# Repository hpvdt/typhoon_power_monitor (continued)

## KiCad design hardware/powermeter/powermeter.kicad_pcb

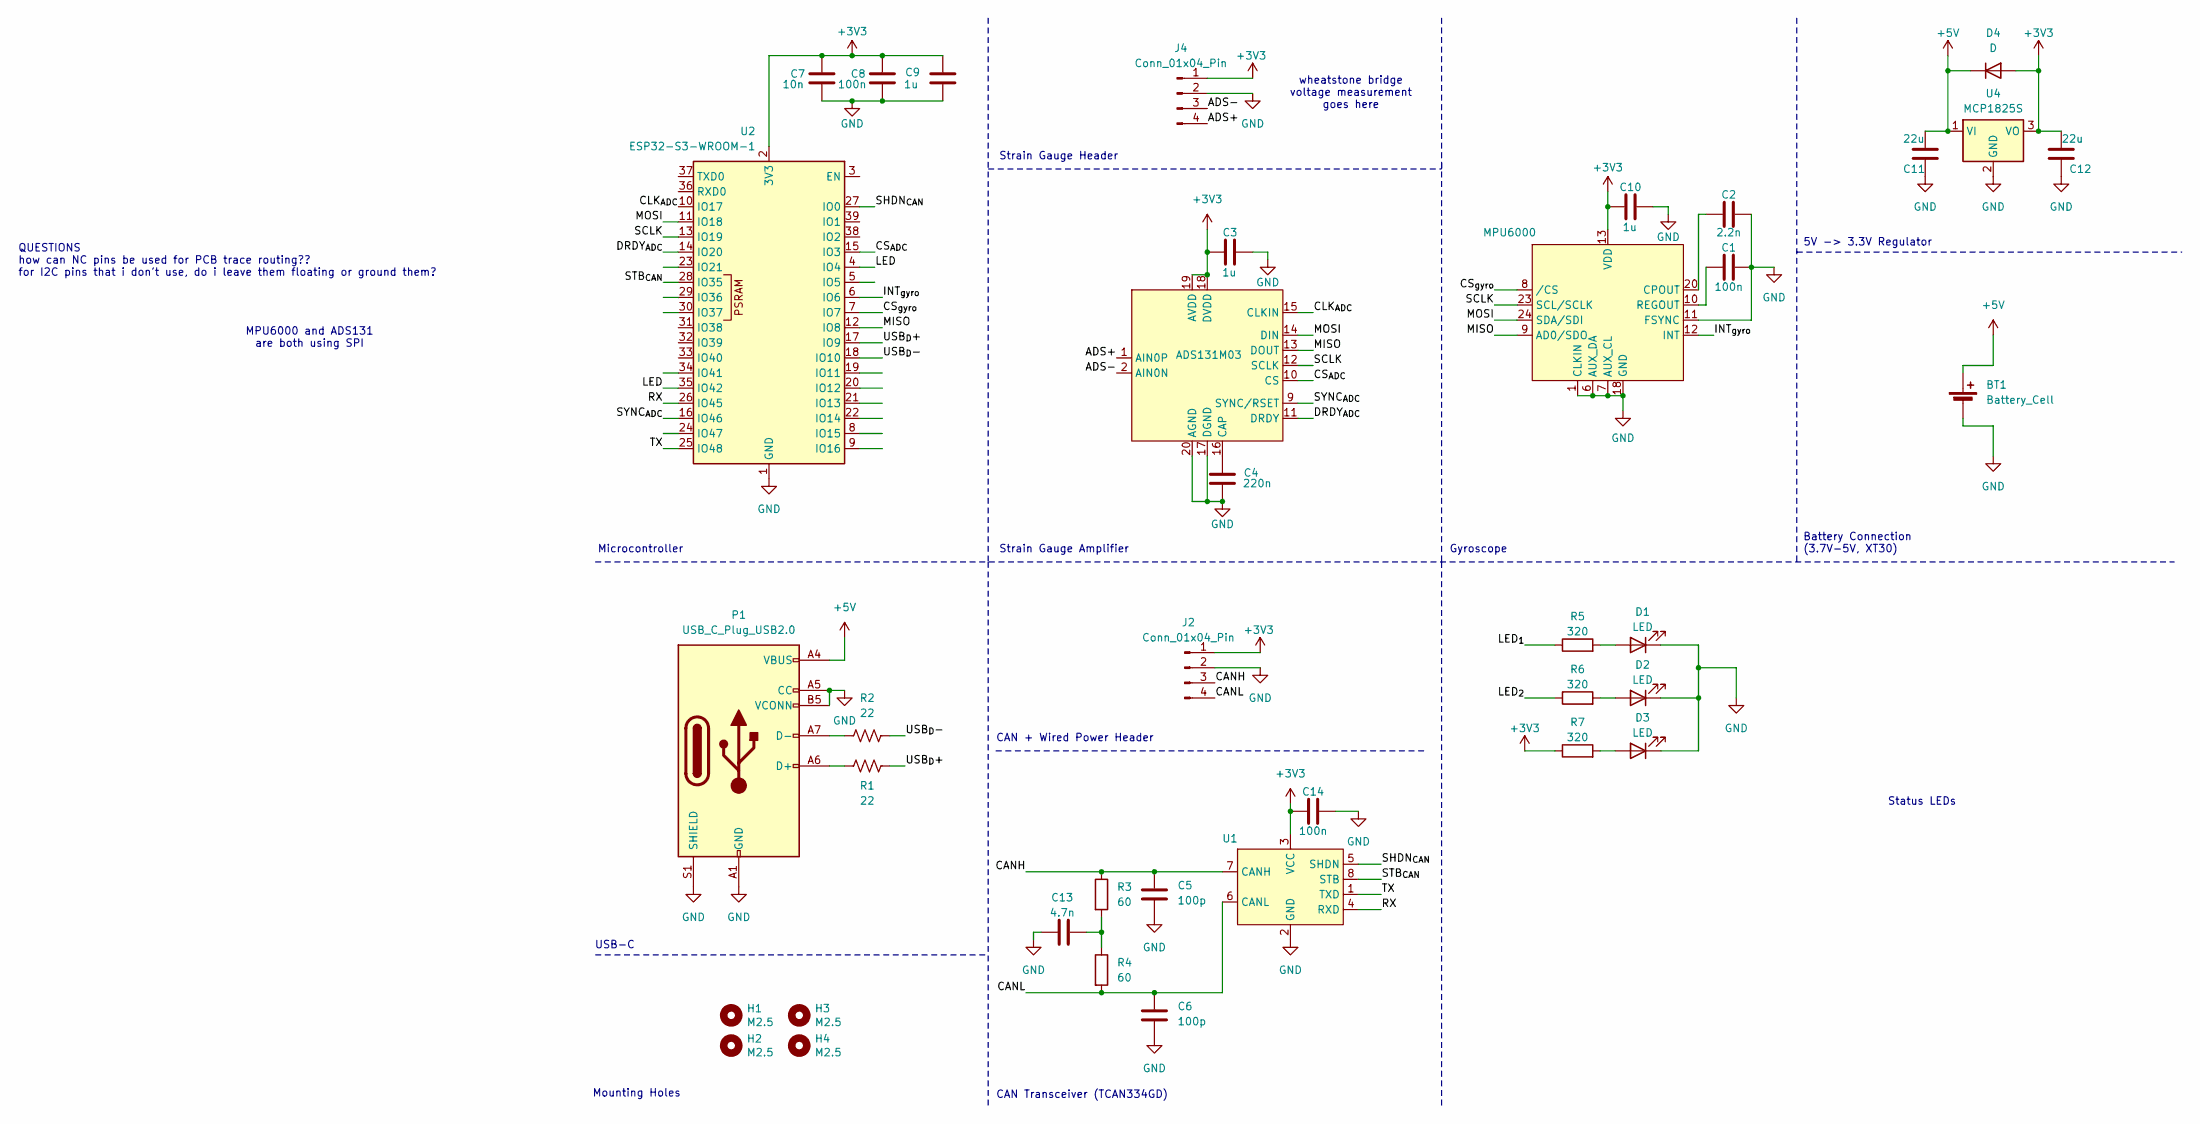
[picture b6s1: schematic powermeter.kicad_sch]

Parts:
ADS131M03: ads
BT1: Battery_Cell; AMASS_XT30U-M_1x02_P5.0mm_Vertical
C1, C8, C14: 100n; C_0402_1005Metric
C2: 2.2n; C_0402_1005Metric
C3, C9, C10: 1u; C_0402_1005Metric
C4: 220n; C_0402_1005Metric
C5, C6: 100p; C_0402_1005Metric
C7: 10n; C_0402_1005Metric
C11, C12: 22u; C_0402_1005Metric
C13: 4.7n; C_0402_1005Metric
D1, D2, D3: LED; LED_0402_1005Metric
D4: D; D_T-1_P5.08mm_Horizontal
H1, H2, H3, H4: M2.5; MountingHole_2.7mm_M2.5
J2, J4: Conn_01x04_Pin; PinSocket_1x04_P2.00mm_Vertical
MPU6000: QFN24_4X4X0P9_IVS
P1: USB_C_Plug_USB2.0; USB_C_Receptacle_HRO_TYPE-C-31-M-12
R1, R2: 22; R_0402_1005Metric
R3, R4: 60; R_0402_1005Metric
R5, R6, R7: 320; R_0402_1005Metric
U1: SO-8_3.9x4.9mm_P1.27mm
U2: ESP32-S3-WROOM-1
U4: MCP1825S; SOT-223-3_TabPin2

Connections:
+3V3: ADS131M03.18 (DVDD), ADS131M03.19 (AVDD), C3.2, C7.2, C8.2, C9.2, C10.2, C12.2, C14.2, D4.2 (A), J2.1, J4.1, MPU6000.13 (VDD), R7.1, U1.3 (VCC), U2.2 (3V3), U4.3 (VO)
+5V: BT1.1 (+), C11.2, D4.1 (K), P1.A4 (VBUS), P1.A9 (VBUS), P1.B4 (VBUS), P1.B9 (VBUS), U4.1 (VI)
/ADS+: ADS131M03.1 (AIN0P), J4.4
/ADS-: ADS131M03.2 (AIN0N), J4.3
/CANH: C5.1, J2.3, R3.1, U1.7 (CANH)
/CANL: C6.1, J2.4, R4.2, U1.6 (CANL)
/CLK_{ADC}: ADS131M03.15 (CLKIN), U2.10 (IO17)
/CS_{ADC}: ADS131M03.10 (CS), U2.15 (IO3)
/CS_{gyro}: MPU6000.8 (/CS), U2.7 (IO7)
/DRDY_{ADC}: ADS131M03.11 (DRDY), U2.14 (IO20)
/INT_{gyro}: MPU6000.12 (INT), U2.6 (IO6)
/LED: U2.4 (IO4), U2.35 (IO42)
/LED_{1}: R5.1
/LED_{2}: R6.1
/MISO: ADS131M03.13 (DOUT), MPU6000.9 (AD0/SDO), U2.12 (IO8)
/MOSI: ADS131M03.14 (DIN), MPU6000.24 (SDA/SDI), U2.11 (IO18)
/RX: U1.4 (RXD), U2.26 (IO45)
/SCLK: ADS131M03.12 (SCLK), MPU6000.23 (SCL/SCLK), U2.13 (IO19)
/SHDN_{CAN}: U1.5 (SHDN), U2.27 (IO0)
/STB_{CAN}: U1.8 (STB), U2.28 (IO35)
/SYNC_{ADC}: ADS131M03.9 (SYNC/RSET), U2.16 (IO46)
/TX: U1.1 (TXD), U2.25 (IO48)
/USB_{D}+: R1.2, U2.17 (IO9)
/USB_{D}-: R2.2, U2.18 (IO10)
GND: ADS131M03.17 (DGND), ADS131M03.20 (AGND), BT1.2 (-), C1.1, C2.1, C3.1, C4.1, C5.2, C6.2, C7.1, C8.1, C9.1, C10.1, C11.1, C12.1, C13.1, C14.1, D1.1 (K), D2.1 (K), D3.1 (K), J2.2, J4.2, MPU6000.1 (CLKIN), MPU6000.6 (AUX_DA), MPU6000.7 (AUX_CL), MPU6000.11 (FSYNC), MPU6000.18 (GND), P1.A1 (GND), P1.A5 (CC), P1.A12 (GND), P1.B1 (GND), P1.B5 (VCONN), P1.B12 (GND), P1.S1 (SHIELD), U1.2 (GND), U2.1 (GND), U2.40 (GND), U2.41 (GND), U4.2 (GND)
unnamed: ADS131M03.16 (CAP), C4.2
unnamed: C13.2, R3.2, R4.1
unnamed: D1.2 (A), R5.2
unnamed: D2.2 (A), R6.2
unnamed: D3.2 (A), R7.2
unnamed: C2.2, MPU6000.20 (CPOUT)
unnamed: C1.2, MPU6000.10 (REGOUT)
unnamed: P1.A6 (D+), R1.1
unnamed: P1.A7 (D-), R2.1

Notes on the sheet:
Strain Gauge Header
Strain Gauge Amplifier
wheatstone bridge voltage measurement goes here
CAN + Wired Power Header
Status LEDs
Mounting Holes
Microcontroller
5V -> 3.3V Regulator
MPU6000 and ADS131 are both using SPI
Battery Connection (3.7V-5V, XT30)
QUESTIONS how can NC pins be used for PCB trace routing?? for I2C pins that i don't use, do i leave them floating or ground them?
Gyroscope
USB-C
CAN Transceiver (TCAN334GD)

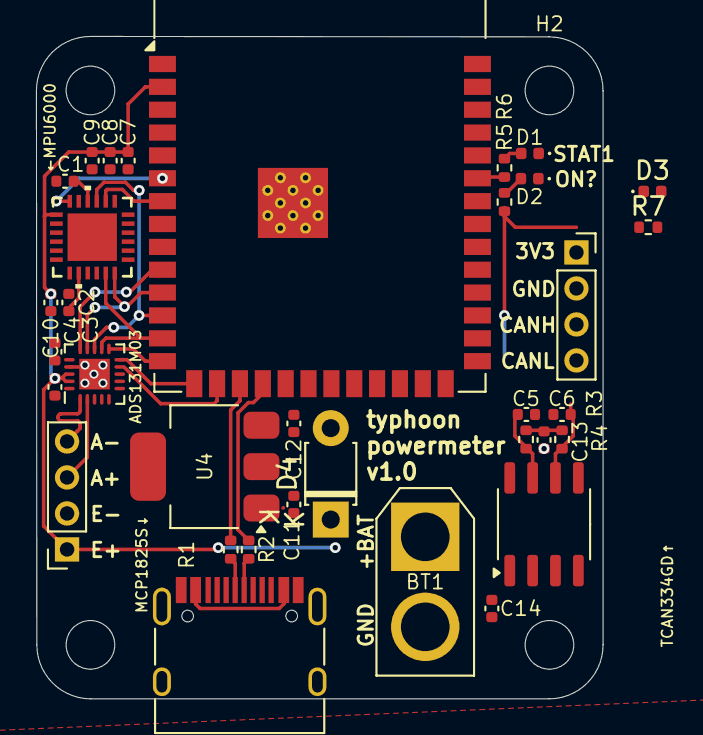
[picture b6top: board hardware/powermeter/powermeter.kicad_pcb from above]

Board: 2 copper layers, 31.5 x 36.8 mm, 38 parts (0 on the bottom side), 32 nets.

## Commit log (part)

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2024-07-12 copied everything from old repo to here
2024-08-04 board layout redesign, swapped transceiver, added misc components
2024-08-04 moving stuff to new repo + board layout redesign
2024-08-04 swapped imu, minor changes, renaming
2024-08-04 redid some traces
2024-08-06 added back silkscreen
2024-10-29 Comments
2024-10-31 major changes
2024-11-17 Final Check and did the production files
2025-07-14 Rev 2 Initial Files
2026-02-03 create nexus_power_rev3
2026-02-03 Added Hello World for Firmware
    Needed to hot plug EN and IO0 to high (Pack it up)
2026-02-04 Organized rev3 and rev4
    Organized rev3 and rev4
2026-02-07 Update for resolder
    added pull up resistors and changed j2 footprint
2026-02-20 fixed up things for justin to look
    fixed up things for justin to look
2026-02-25 Fixed schematic based on Noah's notes from Justin
2026-02-27 Updated PCB and schematic for esp32 s3 wroom
2026-02-27 Rewired the HX711 on pcb and shrunk pcb size
2026-02-28 Fixing up PCB
    added pull up resistor, replaced esp footprint, added header
    made are a lot smaller
2026-03-01 created BOM
    updated symbol fields
2026-03-02 connected TX and RX pins on MCU to header
2026-03-02 last fixes
    moved usb cconnector to edge, added more silkscreen, added tx and rx to breakout header
2026-03-04 Final fixes
2026-03-05 Added board maker name
2026-04-11 rev5 files
2026-04-11 UPDATE HEADER
2026-04-19 Rev 5 changes
2026-04-20 wired the pcb
2026-04-20 small changes to the traces
2026-04-20 fixed header traces
2026-04-21 Final touchups and cleaned up layout
